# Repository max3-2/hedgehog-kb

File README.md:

# Hedgehog

A 60ish keyboard with a new plate-case design. This has been heavily inspired
by the layout of [Purple Owl](https://github.com/SonalPinto/purple-owl) but I
wanted a more programmer friendly right side with larger modifier keys. So I
changed some keys and also redesigned the PCB to use a more standard
QMK approach. With LED support and some good keycaps, I think it is a great
looking compact keyboard!

The typing is damped by the felt layer but quite stable due to the pretty firm
brass plate. The springs keep the plate in place but allow some flex as designed.
Sound is really good for what I expected, but I added foam on the plate and
without it the brass plate will be pingy with the missing support in the center.

TL;DR: Pricing and surplus parts listed at the end!

TL;DR 2: Some upcoming improvements listed at the end

## Status

- I will add some feet, no angle is just too flat too type. ETA unknown.
- Plates and weights have arrived, assembly finalized!
- Case assembled, only plate and weight left, ETA see below.
- Case parts have arrived.
- Plated ETA at 15/11, felt layer ETA 15/11, case parts also ordered with no
ETA. Pricing see below.
- PCBs have arrived and tested good.
- Found plate manufacturer, plates and weight will be brass laser cut. Plate
will have engraving. Cost listed below, comparably cheap for low amount of parts
and a strong reduction in cost with more parts expected.
- Sourcing part manufacturers for casing.
- Case design finished.
- Ordered PCBs for Daughterboard and Keyboard.
- PCB design done.

## Layout

The layout is somewhat odd. The aim was to have a good amount of modifiers
and still keep the interesting stagger and a trapezoidal shape. This lead to the
removal of the nav cluster, thus this is the initial lite version. I might create
another one with arrow cluster and going for a parallelogram shape. Final
layout ended up like this

## Assembly

Final assembly is described here in good detail with the parts I ordered for
the first batch, if you make your own parts some steps might need adaption. Any
question, just let me know!

With all parts produced, the case assembly comes first. See below for how I
proceeded given the parts I had with just laser cutting. Bolts are M3 x 12.
Keep in mind to install the daughterboard in between the case rings or just use
two screws. Weight needs shorter bolts, M3 x 5 work or just cut down some
longer ones.

I then added switch pads and plate foam to PCB and plate, since brass plates
often tend to be a little pingy. I chose some generic KBDfans stabilizers which
was a bad choice since they rattle. Next re-assembly, I'll change to some better
ones.

Finally, assemble plate and PCB with switches (Tangerines linear):

Place felt on case and align, place plate with PCB, and screw down with a soft
washer, spring (see below in parts table) and bolt using the same M3 x 12. Done!
Just add some keycaps, I chose PBTfans Resonance. Base Kit and 40s are a good
fit, sometimes base kit is enough, just need the split spacebars.

#### Plate and Case

##### Plate

Plates and weights were laser cut but the first batch has issues with
tolerances and surface quality. The engraving, especially, is barely visible.
I tried to glassbead blast two samples which increased surface feel quality
and produced usable samples. The engraving however vanishes. I have the leftover
plates if someone wants them but keep those issued in mind.

Same for the weights - but they are invisible. So for those I just cut the
two threads and sanded them down a bit.

##### Case

Case acrylic parts have been produced. Cut quality is acceptable. This prototype is
built with four layers just 2D cut, so some steps remain in creating the case:
First, countersink the screw holes in the bottom (also, from the bottom side).
I have a drill press, if by hand try to keep it as symmetric as possible. I then
went on to cut the M3 threads for the six bolts for case assembly, which are
only cut in the uppermost acrylic part. Pre-assemble two (in my case blue) top
rings and cut five threads, M3, for plate from top. With only two rings you can
cut the threads in an open hole and don't need to worry about the blind holes.
Finally, assemble the four acrylic parts (bottom, frosted ring, blue ring, top
blue ring). Place felt layer (in my case orange) on top. Some impressions:

#### PCB

PCBs have arrived and look quite cool. All features seem to work! Tested both FWs
and all buttons, LEDs and other features work as expected.
**TL;DR** *No need to solder any headers and ISP, out of the box PCBs accept
initial firmware using `qmk flash` over USB!* Thanks, ATMEL (I guess, but please
update your documentation!).

More informations? Keep on reading...

First thing I noticed is that I chose a 1.27mm spacing for ISP which I did not
have around, so I had to fetch some
headers. Soldering is quite annoying at that pitch but doable. Next up was an
adapter for my ISP programmer which again was for 2.54mm spacing. Again very
fiddly. Should've tested before to avoid some burnt fingers.
Finally, solder RST switch at the front, thats quite easy.

For an initial check if everything is hooked up run
```
> avrdude -c usbasp -p m32u4

avrdude: AVR device initialized and ready to accept instructions

Reading | ################################################## | 100% 0.00s

avrdude: Device signature = 0x1e9587 (probably m32u4)
```
seems good, check the fuses:
```
>  avrdude -c usbasp -p m32u4 -U lfuse:r:-:h -U hfuse:r:-:h -U efuse:r:-:h

avrdude: AVR device initialized and ready to accept instructions

Reading | ################################################## | 100% 0.00s

avrdude: Device signature = 0x1e9587 (probably m32u4)
avrdude: reading lfuse memory:

Reading | ################################################## | 100% 0.00s

avrdude: writing output file "<stdout>"
0x5e
avrdude: reading hfuse memory:

Reading | ################################################## | 100% 0.00s

avrdude: writing output file "<stdout>"
0x99
avrdude: reading efuse memory:

Reading | ################################################## | 100% 0.00s

avrdude: writing output file "<stdout>"
0xf3

avrdude done.  Thank you.
```
Perfect, nothing to change here. Mind that `JTAG` is on but that should not be
of an issue here. Go ahead and flash the firmware (just use production, which
includes a bootloader!)

```
avrdude -c usbasp -p m32u4 -U flash:w:11kbd_hedgehog_lite_default_production.hex

avrdude: AVR device initialized and ready to accept instructions

Reading | ################################################## | 100% 0.00s

avrdude: Device signature = 0x1e9587 (probably m32u4)
avrdude: NOTE: "flash" memory has been specified, an erase cycle will be performed
         To disable this feature, specify the -D option.
avrdude: erasing chip
avrdude: warning: cannot set sck period. please check for usbasp firmware update.
avrdude: reading input file "11kbd_hedgehog_lite_default_production.hex"
avrdude: input file 11kbd_hedgehog_lite_default_production.hex auto detected as Intel Hex
avrdude: writing flash (32768 bytes):

Writing | ################################################## | 100% 8.60s

avrdude: 32768 bytes of flash written
avrdude: verifying flash memory against 11kbd_hedgehog_lite_default_production.hex:
avrdude: input file 11kbd_hedgehog_lite_default_production.hex auto detected as Intel Hex

Reading | ################################################## | 100% 7.41s

avrdude: 32768 bytes of flash verified

avrdude done.  Thank you.
```
Perfect, you can test the PCB now and / or test the bootloader by flashing a
new firmware using QMK (after copying the folders or running from the repo)
```
qmk flash -kb 11kbd/hedgehog_lite -km default
```
All works! If you want to prevent changing the FW, just open the slide switch
and any reprogramming will be disabled.

#### Daughterboard

Daughterboards just work out of the box - nothing to add here. Building the
cables, however, is an issue. First, I tried to crimp them myself but even with the
smaller pliers I did not manage to have a good reproducible result. I then just
bought single sided cables and soldered the wires using two ends. Not pretty
but works, and if you look at some shop offers online, it does look to be an
often used workaround.

I did find a custom cable shop in CN which can produce the cables for around
0,40€ per cable but they start at 100pcs so this wasn't a good option here.
Maybe if some group buy will run at some point, I will follow this route. For
now, !no cables are available from my side!

## PCB Details

The PCB is a basic QMK capable **ATmega32U4** row-col setup, using 9 rows and
9 columns. The PCB was designed in KiCAD and the current design is somewhere
between WiP and ready for a prototype. Cool features include a good number of
underglow (15) LEDs and some flex cuts. Switch sockets are hotswap and layout
is a single fixed one, derived from ANSI. No stepped caps or any splits at this point.

The USB connection is a JST with support for *Unified Daughterboard* by **ai03**
which make the PCB able to move and flex and saves some space. Also, feel free
to adapt the case to place the USB wherever you want.

There are, compared to other PCBs out there, some smaller quirks and features
which are notable:
- The PCB uses a *M*-variant of the AtMega due to shortages and prices hikes of
the more common *A*-variant. Also, this one is a little more compact.
- The implemented *M*-variant has **no USB bootloader** flashed. Initially,
this has to be done (or not see above). Using a basic *ISP* programmer,
check the fuses and if needed set them to the QMK values (which are good for
external oscillator). Afterwards, USB flashing using *RST* over USB *should*
work (confirm that *HWB* switch is closed!). See assembly section for details!
- LED power supply is activated with a solder jumper. This reduces current
during initial flash and allows to leave LEDs disabled in non-translucent cases.
- HWB pin is connected with a switch. So by either not soldering this in or
setting to open position bootloader access and flashing can be preventing and
also reducing startup time / room for errors. A jumper exists to fully override
the switch.
- Reset switch is placed on bottom ("top" during use) layer below spacebar so
resetting can be done with case fully assembled.

The above should make it clear that **even with an assembled PCB** minimal
soldering is required for full functionality. I will only have one PCB side
assembled to save money - so when **using this procedure or leftover PCBs**.
I might offer the reset switch has to be placed and soldered afterwards to allow
bootloader flash.

## Case and Mount Details

Case will be designed for either laser cutting or printing / milling. Currently,
the case is layered for cutting so some cutouts aren't perfect but milling is
not feasible in prototyping and small batch. Current color design is frosted
bottom, blue mid, warm yellow felt and brass plate. Overall height will be 16.5mm
to plate surface. Feets are optional and might get added to tent the whole case.

Bottom and three rings (one acrylic, two blue, split not visible in render)
will be screwed from below. Plate will be screwed from top into preassembled
bottom.

Plate is designed to be aluminum or brass, and the plate mount is done via a
felt / cork dampening layer and springs. Plate logo is optional depending on
engraving capabilities of specific shops.

Initial CAD renders below showing top, spring mount in comparison with
switch size and the connector which is currently placed at the left side.

## Name
Because its autumn and that's the perfect time for them!

## Cost breakdown

Obviously, this is a prototype / small batch so pricing will a) comparable high
and b) differ in different locations. Also, due to my profession, I do have some
connection which make some of the steps easier. Cost is listed for an order
of (at least) five keyboards. Second to last column shows parts which are surplus
(contact me if you are interested!)

| **Part** | **Produced by / at** | **Price** | **# available** | **Remark** |
|----------|----------------------|-----------|-----------------|------------|
| Main PCB | JLCPCB assembled | 35€ | 3 | One side assembled, RST switch and jumpers need soldering, parts included. |
| Unified Daughterboard (with cable) | JLCPCB assembled | 10€ | 3 | PCB is 1.2mm for increased spacing! |
| Brass plate 1.5mm | Local shop | 35€ | 3 | Price includes engraved hedgehog and basic removal of burrs. Might glassbead blast it later for satin looks. |
| Brass weight 2mm | Local shop | 10€ | 3 | Only two millimeter due to material availability - will add some weight and looks! |
| Case lower frosted acrylic | Local shop | 25€ | none | No discount for multiple parts |
| Case mid colored acrylic | Local shop | 35€ | none | No discount for multiple parts |
| Felt damper | Local shop | 8€ | 3 |  |
| Springs | Local shop | 2€ / pc. | 6 | I choose 6mm free length and compress them to approx. 3mm which generates 3N per spring. Inner diameter should match M3 (>3.5mm) and outer should not be much more than 5mm |
| Hardware | Local shop | - | - | M3 x 12, M3 x 5, Nylon washers M3 |

## ToDos for a V1.1

- Improve GND on PCB for controller. Not needed since it works really good but
better practice
- Improve plate manufacture or / and increase switch opening size. The current
dimensioning is ok but fairly tight.
- Do the same for the stabs, if possible add at least 1mm left / right for the
stems
- Find a way to keep the felt layer aligned, currently it tends to slide around
a bit - purely a visual error but still needs improving.
- Add some more layout options: Switch BS, Mod key right of return, ISO?

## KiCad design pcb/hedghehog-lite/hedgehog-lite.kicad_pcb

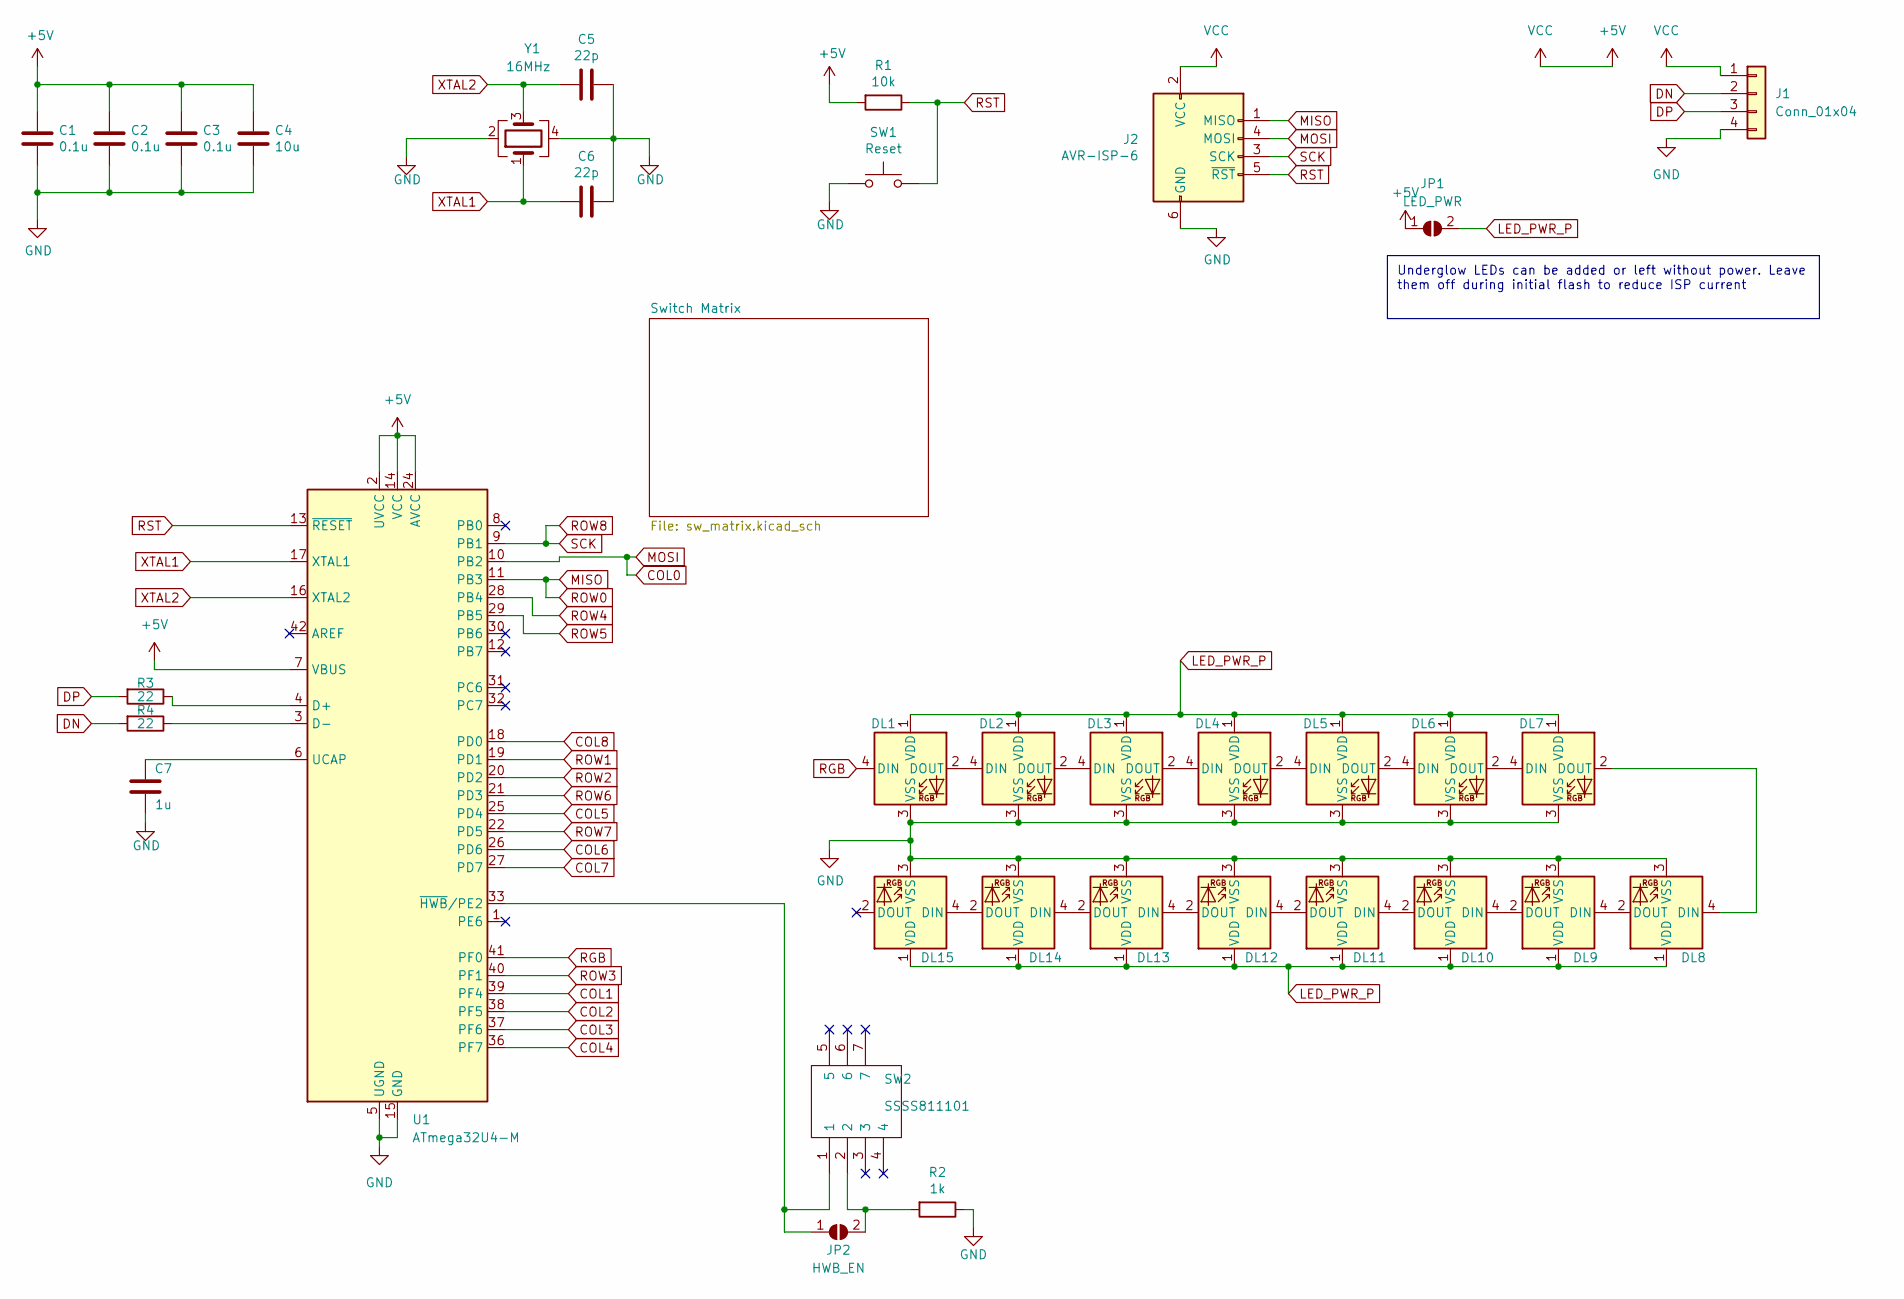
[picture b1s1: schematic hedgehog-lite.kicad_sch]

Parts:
C1, C2, C3: 0.1u; C_0805_2012Metric; LCSC Part # C49678
C4: 10u; C_0805_2012Metric; LCSC Part # C15850
C5, C6: 22p; C_0805_2012Metric; LCSC Part # C1804
C7: 1u; C_0805_2012Metric; LCSC Part # C28323
DL1, DL2, DL3, DL4, DL5, DL6, DL7, DL8, DL9, DL10, DL11, DL12, DL13, DL14, DL15: WS2812B; LED_WS2812B_PLCC4_5.0x5.0mm_P3.2mm; LCSC Part # C2874885
J1: Conn_01x04; JST-SR-4; LCSC Part # C160404
J2: AVR-ISP-6; PinHeader_2x03_P1.27mm_Vertical
JP1: LED_PWR; SolderJumper-2_P1.3mm_Open_RoundedPad1.0x1.5mm
JP2: HWB_EN; SolderJumper-2_P1.3mm_Open_RoundedPad1.0x1.5mm
R1: 10k; R_0805_2012Metric; LCSC Part # C17414
R2: 1k; R_0805_2012Metric; LCSC Part # C17414
R3, R4: 22; R_0805_2012Metric; LCSC Part # C17561
SW1: Reset; SW_SPST_TL3342; LCSC Part # C318884
SW2: SSSS811101; Manufacturer_Part_Number SSSS811101; Mouser Part Number 688-SSSS811101
U1: ATmega32U4-M; QFN-44-1EP_7x7mm_P0.5mm_EP5.2x5.2mm; LCSC Part # C112161
Y1: 16MHz; Crystal_SMD_3225-4Pin_3.2x2.5mm; LCSC Part # C13738

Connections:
+5V: C1.1, C2.1, C3.1, C4.1, J1.1, J2.2 (VCC), JP1.1 (A), R1.2, U1.2 (UVCC), U1.7 (VBUS), U1.14 (VCC), U1.24 (AVCC), U1.34 (VCC), U1.44 (AVCC)
COL0: J2.4 (MOSI), U1.10 (PB2); also elsewhere on the board
COL1: U1.39 (PF4); also elsewhere on the board
COL2: U1.38 (PF5); also elsewhere on the board
COL3: U1.37 (PF6); also elsewhere on the board
COL4: U1.36 (PF7); also elsewhere on the board
COL5: U1.25 (PD4); also elsewhere on the board
COL6: U1.26 (PD6); also elsewhere on the board
COL7: U1.27 (PD7); also elsewhere on the board
COL8: U1.18 (PD0); also elsewhere on the board
DN: J1.2, R4.2
DP: J1.3, R3.2
GND: C1.2, C2.2, C3.2, C4.2, C5.1, C6.1, C7.2, DL1.3 (VSS), DL2.3 (VSS), DL3.3 (VSS), DL4.3 (VSS), DL5.3 (VSS), DL6.3 (VSS), DL7.3 (VSS), DL8.3 (VSS), DL9.3 (VSS), DL10.3 (VSS), DL11.3 (VSS), DL12.3 (VSS), DL13.3 (VSS), DL14.3 (VSS), DL15.3 (VSS), J1.4, J2.6 (GND), R2.1, SW1.1, U1.5 (UGND), U1.15 (GND), U1.23 (GND), U1.35 (GND), U1.43 (GND), U1.45 (GND), Y1.2, Y1.4
LED_PWR_P: DL1.1 (VDD), DL2.1 (VDD), DL3.1 (VDD), DL4.1 (VDD), DL5.1 (VDD), DL6.1 (VDD), DL7.1 (VDD), DL8.1 (VDD), DL9.1 (VDD), DL10.1 (VDD), DL11.1 (VDD), DL12.1 (VDD), DL13.1 (VDD), DL14.1 (VDD), DL15.1 (VDD), JP1.2 (B)
MISO: J2.1 (MISO), U1.11 (PB3); also elsewhere on the board
unnamed: C7.1, U1.6 (UCAP)
unnamed: DL1.2 (DOUT), DL2.4 (DIN)
unnamed: DL2.2 (DOUT), DL3.4 (DIN)
unnamed: DL3.2 (DOUT), DL4.4 (DIN)
unnamed: DL4.2 (DOUT), DL5.4 (DIN)
unnamed: DL5.2 (DOUT), DL6.4 (DIN)
unnamed: DL6.2 (DOUT), DL7.4 (DIN)
unnamed: DL7.2 (DOUT), DL8.4 (DIN)
unnamed: DL8.2 (DOUT), DL9.4 (DIN)
unnamed: DL10.2 (DOUT), DL11.4 (DIN)
unnamed: DL9.2 (DOUT), DL10.4 (DIN)
unnamed: DL11.2 (DOUT), DL12.4 (DIN)
unnamed: DL12.2 (DOUT), DL13.4 (DIN)
unnamed: DL13.2 (DOUT), DL14.4 (DIN)
unnamed: DL14.2 (DOUT), DL15.4 (DIN)
unnamed: JP2.1 (A), SW2.1, U1.33 (~HWB/PE2)
unnamed: JP2.2 (B), R2.2, SW2.2
unnamed: R3.1, U1.4 (D+)
unnamed: R4.1, U1.3 (D-)
RGB: DL1.4 (DIN), U1.41 (PF0)
ROW1: U1.19 (PD1); also elsewhere on the board
ROW2: U1.20 (PD2); also elsewhere on the board
ROW3: U1.40 (PF1); also elsewhere on the board
ROW4: U1.28 (PB4); also elsewhere on the board
ROW5: U1.29 (PB5); also elsewhere on the board
ROW6: U1.21 (PD3); also elsewhere on the board
ROW7: U1.22 (PD5); also elsewhere on the board
ROW8: J2.3 (SCK), U1.9 (PB1); also elsewhere on the board
RST: J2.5 (~RST), R1.1, SW1.2, U1.13 (~RESET)
XTAL1: C6.2, U1.17 (XTAL1), Y1.1
XTAL2: C5.2, U1.16 (XTAL2), Y1.3

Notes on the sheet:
Underglow LEDs can be added or left without power. Leave them off during initial flash to reduce ISP current

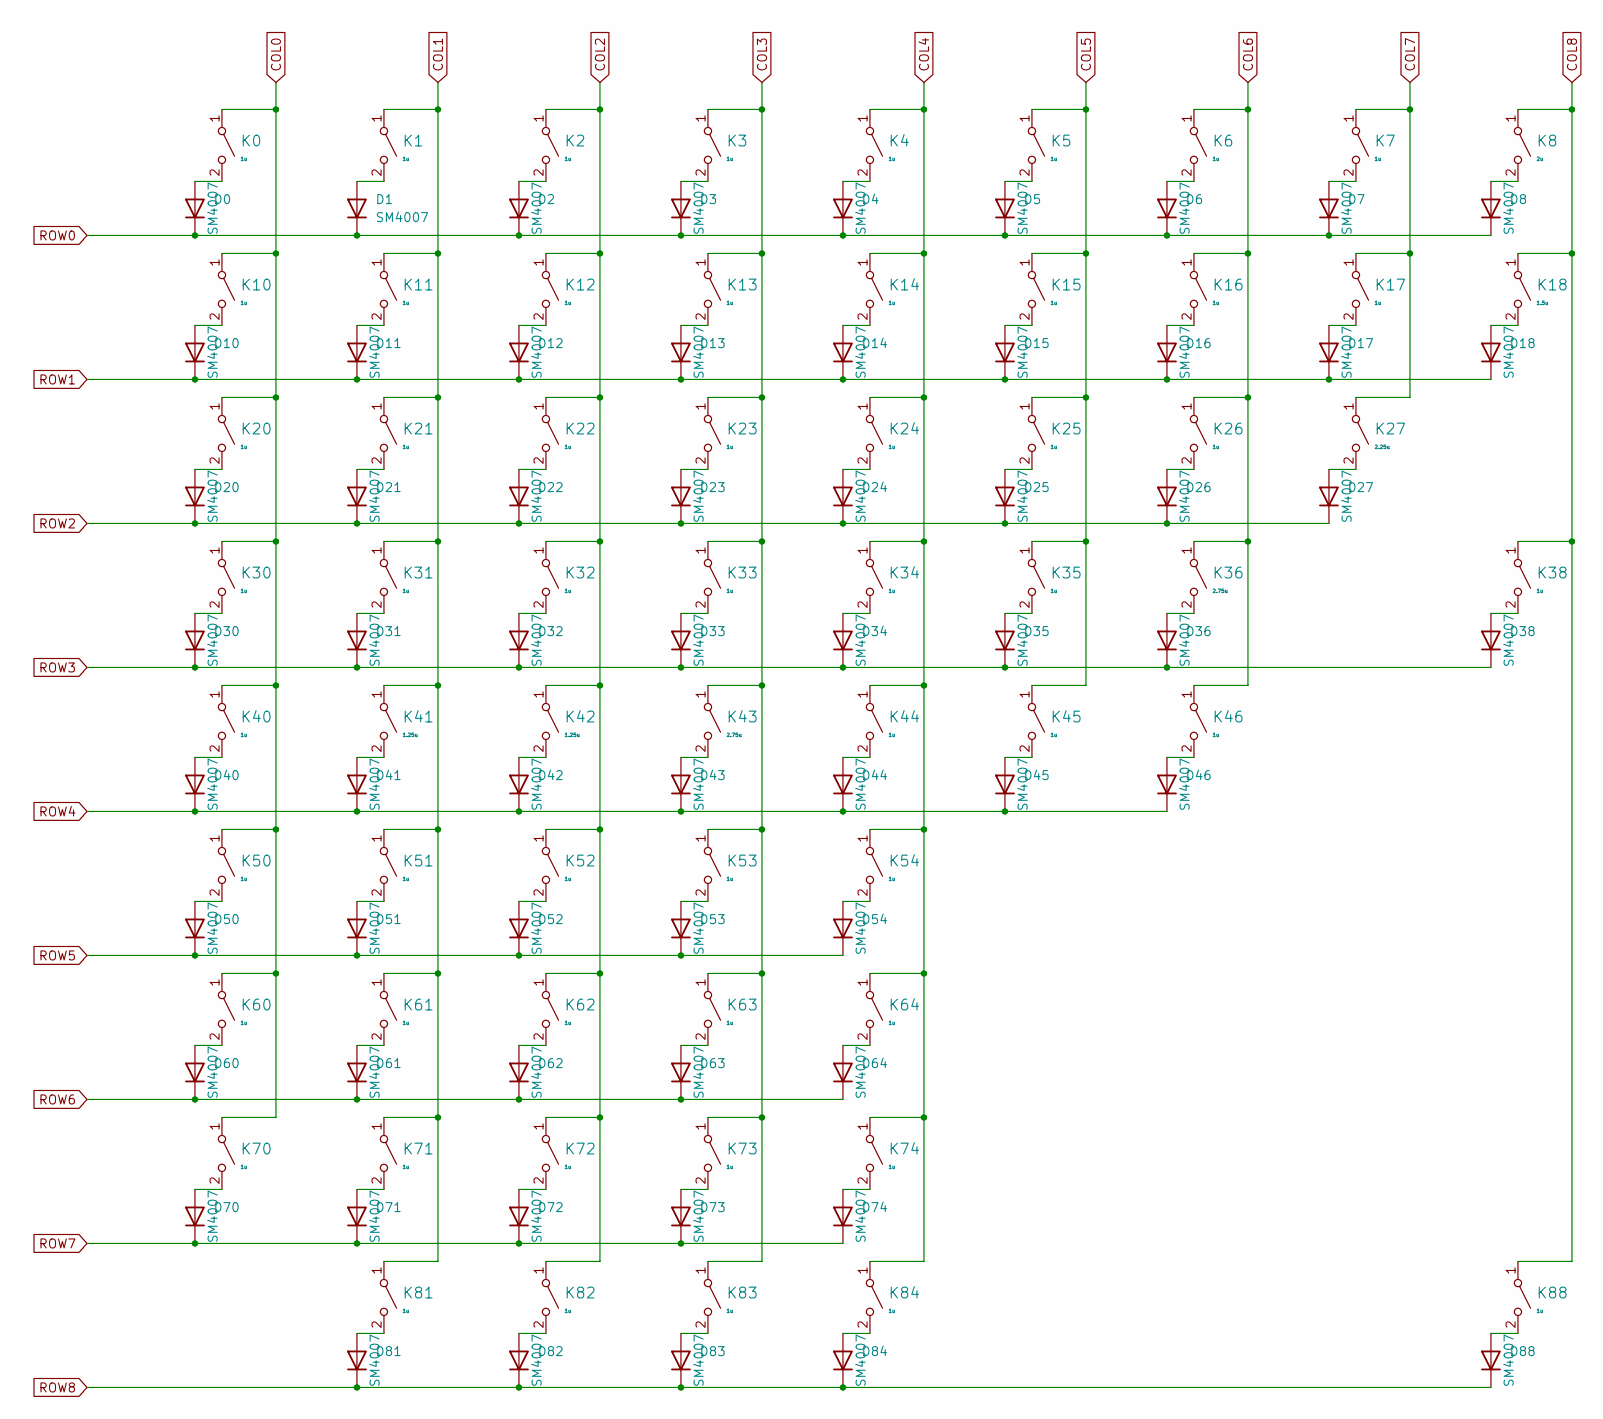
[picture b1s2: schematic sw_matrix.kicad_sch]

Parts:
D0, D1, D2, D3, D4, D5, D6, D7, D8, D10, D11, D12, D13, D14, D15, D16, D17, D18, D20, D21, D22, D23, D24, D25, D26, D27, D30, D31, D32, D33, D34, D35, D36, D38, D40, D41, D42, D43, D44, D45, D46, D50, D51, D52, D53, D54, D60, D61, D62, D63, D64, D70, D71, D72, D73, D74, D81, D82, D83, D84, D88: SM4007; D_SOD-123F; LCSC Part # C64898
K0, K1, K2, K3, K4, K5, K6, K7, K10, K11, K12, K13, K14, K15, K16, K17, K20, K21, K22, K23, K24, K25, K26, K30, K31, K32, K33, K34, K35, K38, K40, K44, K45, K46, K50, K51, K52, K53, K54, K60, K61, K62, K63, K64, K70, K71, K72, K73, K74, K81, K82, K83, K84, K88: 1u; MX100H; LCSC Part # C5156480
K8: 2u; MX200H; LCSC Part # C5156480
K18: 1.5u; MX150H; LCSC Part # C5156480
K27: 2.25u; MX225H; LCSC Part # C5156480
K36: 2.75u; MX275H; LCSC Part # C5156480
K41, K42: 1.25u; MX125H; LCSC Part # C5156480
K43: 2.75u; MX275HR; LCSC Part # C5156480

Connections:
COL0: K0.1 (A), K10.1 (A), K20.1 (A), K30.1 (A), K40.1 (A), K50.1 (A), K60.1 (A), K70.1 (A); also elsewhere on the board
COL1: K1.1 (A), K11.1 (A), K21.1 (A), K31.1 (A), K41.1 (A), K51.1 (A), K61.1 (A), K71.1 (A), K81.1 (A); also elsewhere on the board
COL2: K2.1 (A), K12.1 (A), K22.1 (A), K32.1 (A), K42.1 (A), K52.1 (A), K62.1 (A), K72.1 (A), K82.1 (A); also elsewhere on the board
COL3: K3.1 (A), K13.1 (A), K23.1 (A), K33.1 (A), K43.1 (A), K53.1 (A), K63.1 (A), K73.1 (A), K83.1 (A); also elsewhere on the board
COL4: K4.1 (A), K14.1 (A), K24.1 (A), K34.1 (A), K44.1 (A), K54.1 (A), K64.1 (A), K74.1 (A), K84.1 (A); also elsewhere on the board
COL5: K5.1 (A), K15.1 (A), K25.1 (A), K35.1 (A), K45.1 (A); also elsewhere on the board
COL6: K6.1 (A), K16.1 (A), K26.1 (A), K36.1 (A), K46.1 (A); also elsewhere on the board
COL7: K7.1 (A), K17.1 (A), K27.1 (A); also elsewhere on the board
COL8: K8.1 (A), K18.1 (A), K38.1 (A), K88.1 (A); also elsewhere on the board
MISO: D0.1 (K), D1.1 (K), D2.1 (K), D3.1 (K), D4.1 (K), D5.1 (K), D6.1 (K), D7.1 (K), D8.1 (K); also elsewhere on the board
unnamed: D0.2 (A), K0.2 (B)
unnamed: D1.2 (A), K1.2 (B)
unnamed: D2.2 (A), K2.2 (B)
unnamed: D3.2 (A), K3.2 (B)
unnamed: D4.2 (A), K4.2 (B)
unnamed: D5.2 (A), K5.2 (B)
unnamed: D6.2 (A), K6.2 (B)
unnamed: D7.2 (A), K7.2 (B)
unnamed: D8.2 (A), K8.2 (B)
unnamed: D10.2 (A), K10.2 (B)
unnamed: D11.2 (A), K11.2 (B)
unnamed: D12.2 (A), K12.2 (B)
unnamed: D13.2 (A), K13.2 (B)
unnamed: D14.2 (A), K14.2 (B)
unnamed: D15.2 (A), K15.2 (B)
unnamed: D16.2 (A), K16.2 (B)
unnamed: D17.2 (A), K17.2 (B)
unnamed: D18.2 (A), K18.2 (B)
unnamed: D20.2 (A), K20.2 (B)
unnamed: D21.2 (A), K21.2 (B)
unnamed: D22.2 (A), K22.2 (B)
unnamed: D23.2 (A), K23.2 (B)
unnamed: D24.2 (A), K24.2 (B)
unnamed: D25.2 (A), K25.2 (B)
unnamed: D26.2 (A), K26.2 (B)
unnamed: D27.2 (A), K27.2 (B)
unnamed: D30.2 (A), K30.2 (B)
unnamed: D31.2 (A), K31.2 (B)
unnamed: D32.2 (A), K32.2 (B)
unnamed: D33.2 (A), K33.2 (B)
unnamed: D34.2 (A), K34.2 (B)
unnamed: D35.2 (A), K35.2 (B)
unnamed: D36.2 (A), K36.2 (B)
unnamed: D38.2 (A), K38.2 (B)
unnamed: D40.2 (A), K40.2 (B)
unnamed: D41.2 (A), K41.2 (B)
unnamed: D42.2 (A), K42.2 (B)
unnamed: D43.2 (A), K43.2 (B)
unnamed: D44.2 (A), K44.2 (B)
unnamed: D45.2 (A), K45.2 (B)
unnamed: D46.2 (A), K46.2 (B)
unnamed: D50.2 (A), K50.2 (B)
unnamed: D51.2 (A), K51.2 (B)
unnamed: D52.2 (A), K52.2 (B)
unnamed: D53.2 (A), K53.2 (B)
unnamed: D54.2 (A), K54.2 (B)
unnamed: D60.2 (A), K60.2 (B)
unnamed: D61.2 (A), K61.2 (B)
unnamed: D62.2 (A), K62.2 (B)
unnamed: D63.2 (A), K63.2 (B)
unnamed: D64.2 (A), K64.2 (B)
unnamed: D70.2 (A), K70.2 (B)
unnamed: D71.2 (A), K71.2 (B)
unnamed: D72.2 (A), K72.2 (B)
unnamed: D73.2 (A), K73.2 (B)
unnamed: D74.2 (A), K74.2 (B)
unnamed: D81.2 (A), K81.2 (B)
unnamed: D82.2 (A), K82.2 (B)
unnamed: D83.2 (A), K83.2 (B)
unnamed: D84.2 (A), K84.2 (B)
unnamed: D88.2 (A), K88.2 (B)
ROW1: D10.1 (K), D11.1 (K), D12.1 (K), D13.1 (K), D14.1 (K), D15.1 (K), D16.1 (K), D17.1 (K), D18.1 (K); also elsewhere on the board
ROW2: D20.1 (K), D21.1 (K), D22.1 (K), D23.1 (K), D24.1 (K), D25.1 (K), D26.1 (K), D27.1 (K); also elsewhere on the board
ROW3: D30.1 (K), D31.1 (K), D32.1 (K), D33.1 (K), D34.1 (K), D35.1 (K), D36.1 (K), D38.1 (K); also elsewhere on the board
ROW4: D40.1 (K), D41.1 (K), D42.1 (K), D43.1 (K), D44.1 (K), D45.1 (K), D46.1 (K); also elsewhere on the board
ROW5: D50.1 (K), D51.1 (K), D52.1 (K), D53.1 (K), D54.1 (K); also elsewhere on the board
ROW6: D60.1 (K), D61.1 (K), D62.1 (K), D63.1 (K), D64.1 (K); also elsewhere on the board
ROW7: D70.1 (K), D71.1 (K), D72.1 (K), D73.1 (K), D74.1 (K); also elsewhere on the board
ROW8: D81.1 (K), D82.1 (K), D83.1 (K), D84.1 (K), D88.1 (K); also elsewhere on the board

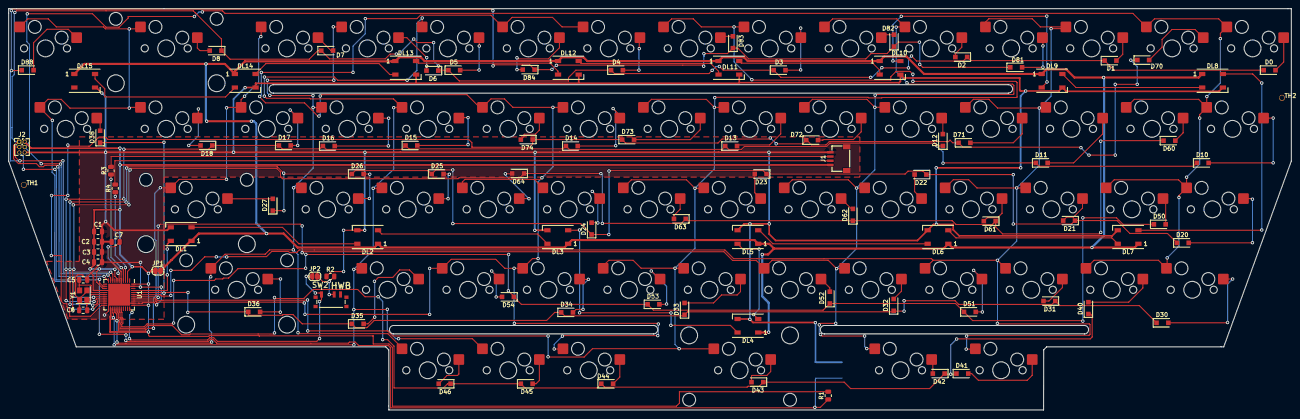
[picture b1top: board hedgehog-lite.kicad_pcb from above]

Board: 2 copper layers, 303.6 x 95.0 mm, 158 parts (1 on the bottom side), 107 nets.

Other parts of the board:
TH1, TH2: jlcpcb_tooling

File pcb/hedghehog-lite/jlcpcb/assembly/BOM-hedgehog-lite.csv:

Comment,Designator,Footprint,LCSC
SSSS811101,SW2,SSSS811101,C109335
ATmega32U4-M,U1,QFN-44-1EP_7x7mm_P0.5mm_EP5.2x5.2mm,C112161
16MHz,Y1,Crystal_SMD_3225-4Pin_3.2x2.5mm,C13738
10u,C4,C_0805_2012Metric,C15850
Conn_01x04,J1,JST-SR-4,C160404
10k,"R1,R2",R_0805_2012Metric,C17414
22,"R3,R4",R_0805_2012Metric,C17561
22p,"C5,C6",C_0805_2012Metric,C1804
1u,C7,C_0805_2012Metric,C28323
WS2812B,"DL1,DL10,DL11,DL12,DL13,DL14,DL15,DL2,DL3,DL4,DL5,DL6,DL7,DL8,DL9",LED_WS2812B_PLCC4_5.0x5.0mm_P3.2mm,C2874885
0.1u,"C1,C2,C3",C_0805_2012Metric,C49678
1u,"K0,K1,K10,K11,K12,K13,K14,K15,K16,K17,K18,K2,K20,K21,K22,K23,K24,K25,K26,K27,K3,K30,K31,K32,K33,K34,K35,K36,K38,K4,K40,K41,K42,K43,K44,K45,K46,K5,K50,K51,K52,K53,K54,K6,K60,K61,K62,K63,K64,K7,K70,K71,K72,K73,K74,K8,K81,K82,K83,K84,K88",MX100H,C5156480
SM4007,"D0,D1,D10,D11,D12,D13,D14,D15,D16,D17,D18,D2,D20,D21,D22,D23,D24,D25,D26,D27,D3,D30,D31,D32,D33,D34,D35,D36,D38,D4,D40,D41,D42,D43,D44,D45,D46,D5,D50,D51,D52,D53,D54,D6,D60,D61,D62,D63,D64,D7,D70,D71,D72,D73,D74,D8,D81,D82,D83,D84,D88",D_SOD-123F,C64898

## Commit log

2022-09-26 Added layout for first version
    Lite will be the initially produced layout without nav cluster
2022-09-26 Initial firmware blueprint
2022-09-27 Ignore kicad backups
2022-09-27 More edits to the schematic building v1
2022-09-28 Added PCB Slider part
2022-09-28 Placed all components on PCB
2022-09-28 Moved pin header to allow left side conn
2022-09-28 Cleanup, better placement, ready to wire
2022-09-30 Wiring up all parts, excluding matrix
2022-10-01 Added edge cuts
2022-10-02 all done but switches
2022-10-02 Columns wired up
2022-10-02 Fixed 3d models
2022-10-02 Top Row done
2022-10-02 All routing done
2022-10-03 PCB cleanup
2022-10-03 Added documentation
2022-10-03 Small PCB improvements
2022-10-03 Initial fabrication files and update to Kailh socket parts
2022-10-03 Added logos CR
2022-10-03 Added MIT License
2022-10-03 Updated pcb images
2022-10-03 Removed redundant svgs
2022-10-04 Re-checked layout
2022-10-04 Created plate and pcb outlines
2022-10-04 KiCad fabrication prepare
2022-10-04 Fixed README typos and small issues
2022-10-05 Added axis origin and pcb step file
2022-10-06 Addced logos as pngs and renders
2022-10-06 Small corrections to README
2022-10-07 Added assembly files and pos fixer for kailh
2022-10-07 Small PCB fixes and improvements
2022-10-07 Updated fab files
2022-10-08 Ignore macOS tables
2022-10-08 Initial firmware which builds
    Including a rename to prevent hyphen issues
2022-10-08 Added advanced keymap blueprint
    This will have more layers and features and is a ToDo
2022-10-08 Added production firmware
    This is a combination of default keymap and bootloader
2022-10-11 Readme fixes
2022-10-11 Improved ReadMe
2022-10-11 Added a smaller logo as dxf for engraving
2022-10-11 Added dxfs for laser cutting case parts
2022-10-19 Improved GND connection for atmega
    This should not be needed but now all pins are connected to an external track
2022-10-21 Reordered status timeline, added plate and weight details
2022-10-22 Fixed LED issues in firmware
2022-10-22 Fixed production firmware
2022-10-22 Added details on PCBs and plate manufacture
2022-10-22 Reformat and fix README
2022-10-22 Added details on case order
2022-10-22 Updated layout image with correct MOD
2022-10-26 Moved FW source to QMK fork
    see https://github.com/max3-2/qmk_firmware
2022-11-05 Added more on Fab and images, more to come!
2022-11-05 Small name fixes in README
2022-11-11 Added final assembly and images to README
2022-11-11 Updated prod firmware with newest fixes
2022-11-11 Some more small details in README

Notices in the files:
pcb/hedghehog-lite/hedgehog-lite.kicad_pcb:
© git: max3-2
